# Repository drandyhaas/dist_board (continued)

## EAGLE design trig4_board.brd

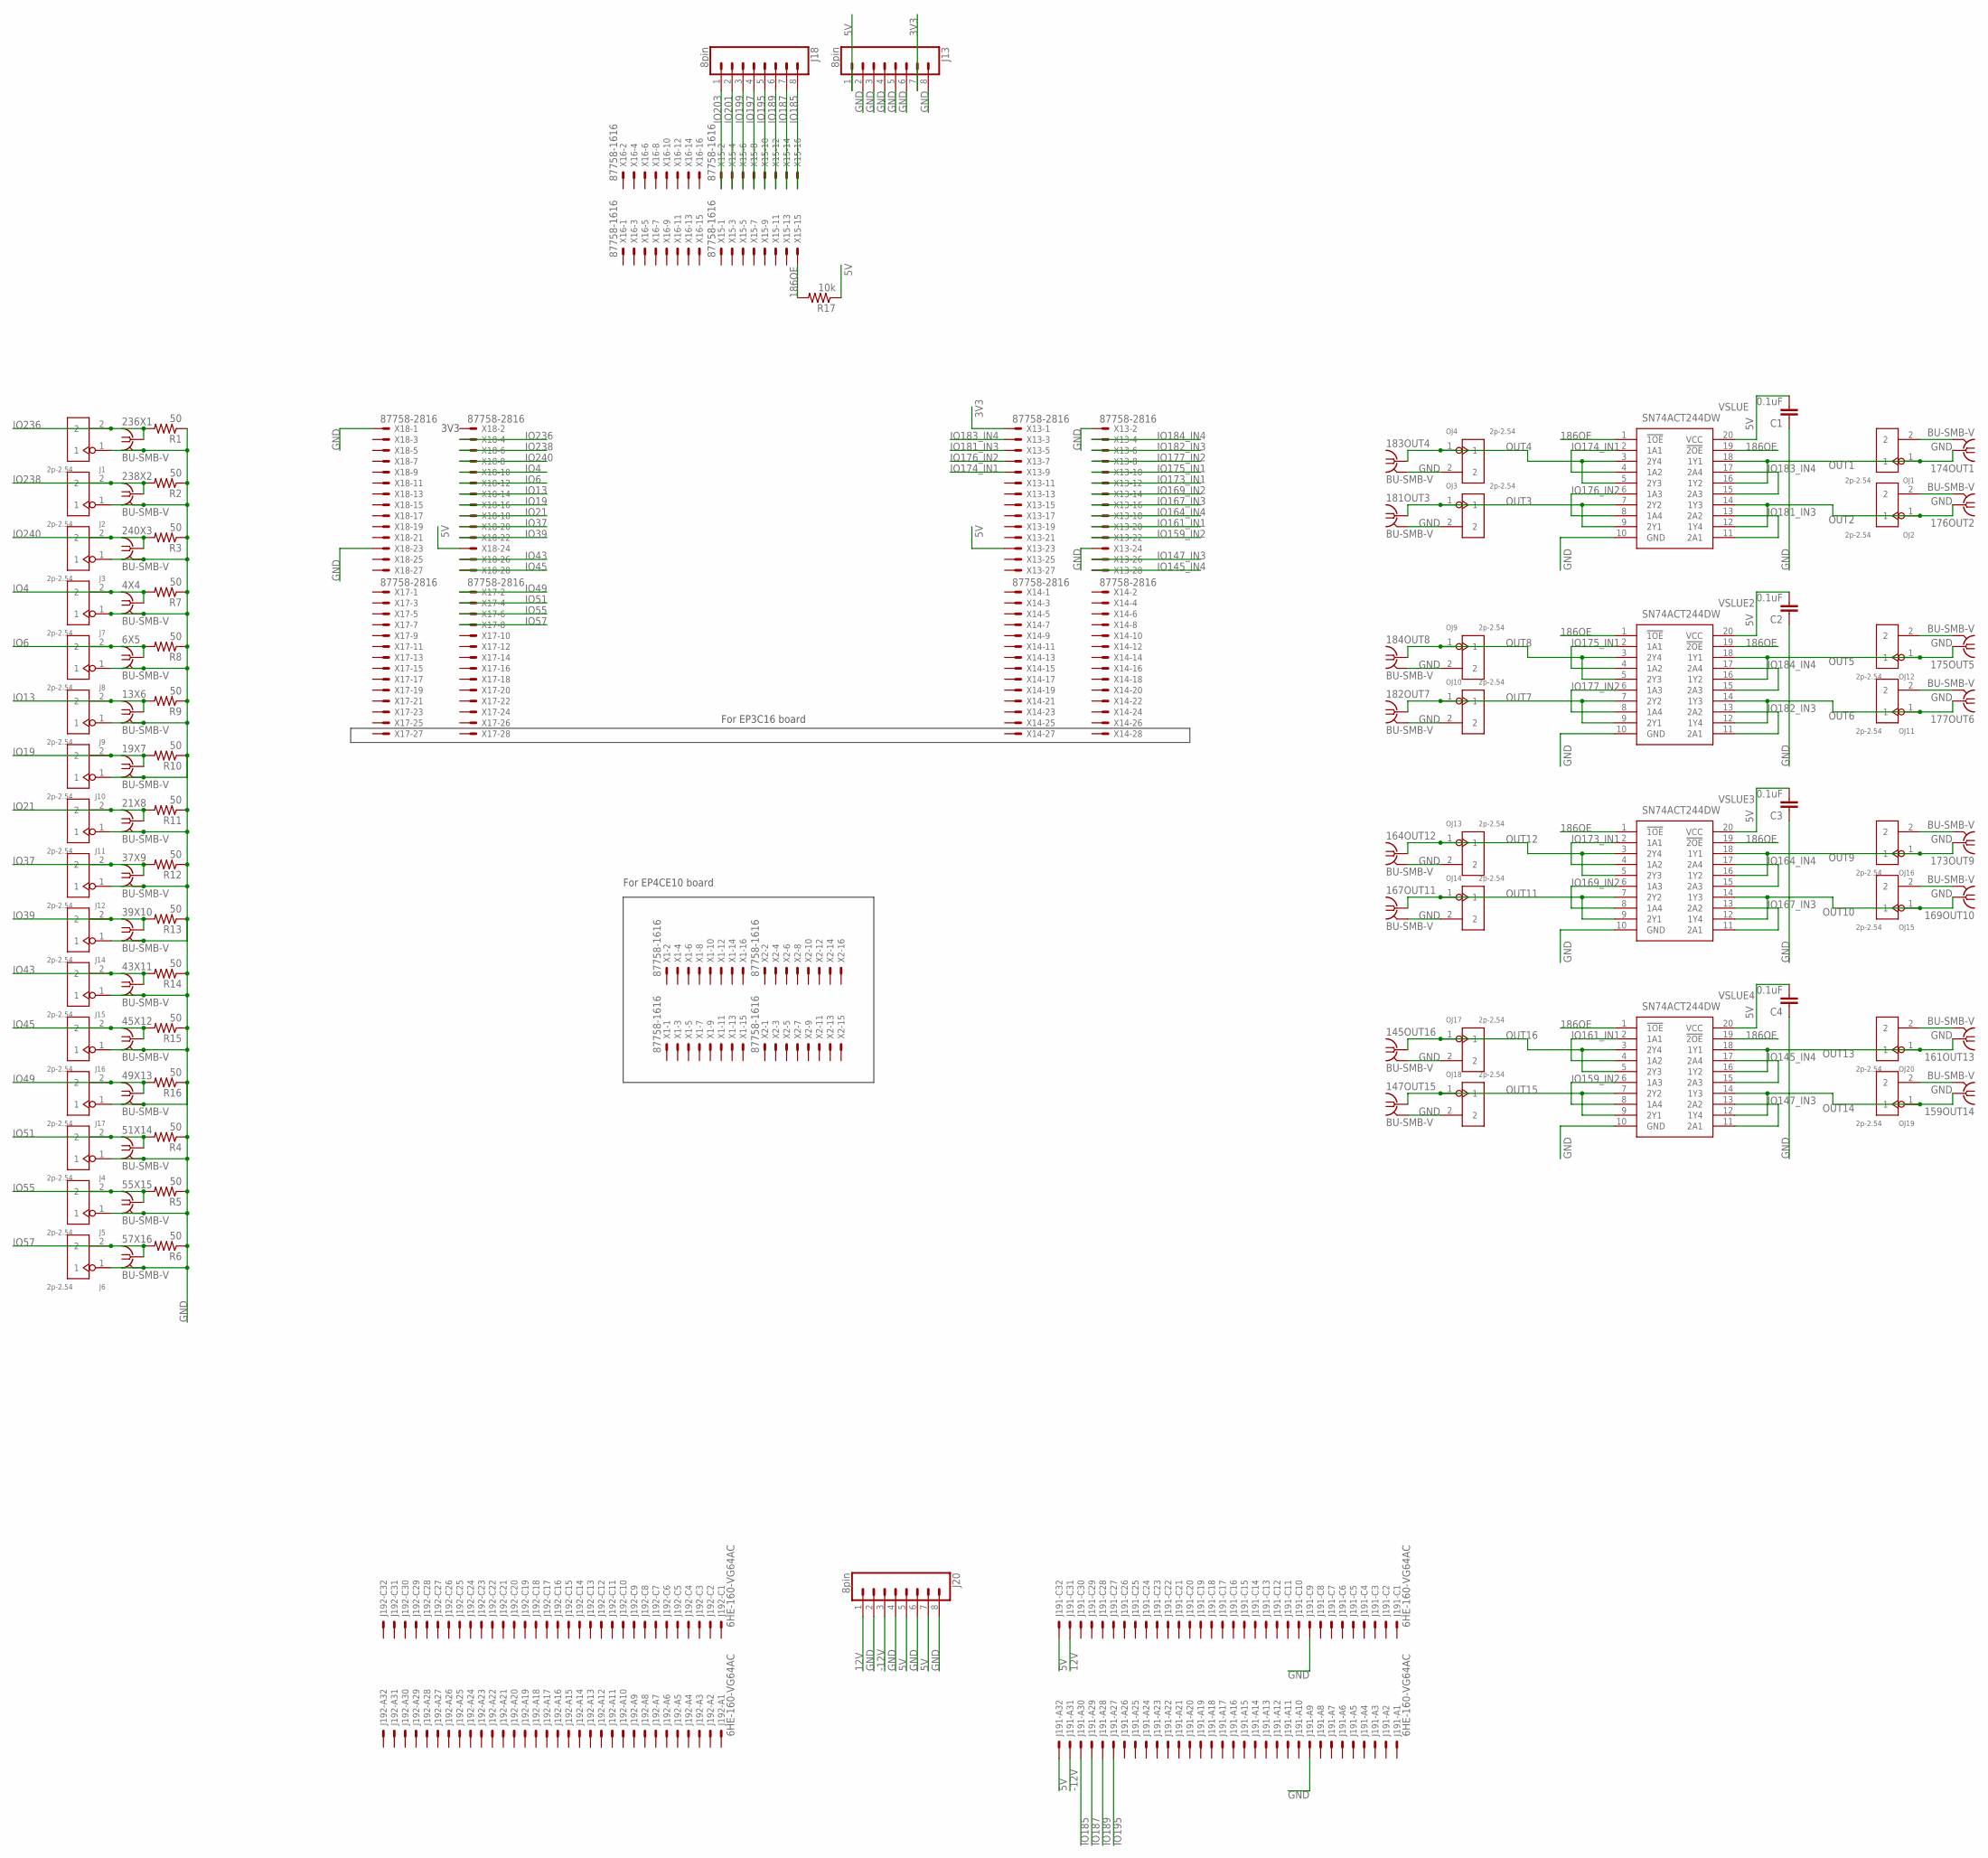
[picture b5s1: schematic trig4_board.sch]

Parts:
4X4, 6X5, 13X6, 19X7, 21X8, 37X9, 39X10, 43X11, 45X12, 49X13, 51X14, 55X15, 57X16, 145OUT16, 147OUT15, 159OUT14, 161OUT13, 164OUT12, 167OUT11, 169OUT10, 173OUT9, 174OUT1, 175OUT5, 176OUT2, 177OUT6, 181OUT3, 182OUT7, 183OUT4, 184OUT8, 236X1, 238X2, 240X3: BU-SMB-V
C1, C2, C3, C4: 0.1uF; 0805
J1, J2, J3, J4, J5, J6, J7, J8, J9, J10, J11, J12, J14, J15, J16, J17: 2p-2.54; H2-2.54
J13, J18, J20: 8pin; 1X08
J19: 6HE-160-VG64AC; 6HE_160-VG64AC
OJ1, OJ2, OJ3, OJ4, OJ9, OJ10, OJ11, OJ12, OJ13, OJ14, OJ15, OJ16, OJ17, OJ18, OJ19, OJ20: 2p-2.54; H2-2.54
R1, R2, R3, R4, R5, R6, R7, R8, R9, R10, R11, R12, R13, R14, R15, R16: 50; AXIAL-0.3
R17: 10k; AXIAL-0.3
VSLUE, VSLUE2, VSLUE3, VSLUE4: SN74ACT244DW; SOIC127P1030X265-20N
X1, X2, X15, X16: 87758-1616
X13, X14, X17, X18: 87758-2816

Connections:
3V3: J13.7, X13.1
5V: C1.2, C2.2, C3.2, C4.2, J13.1, J19.1-A32 (MS), J19.1-C32 (MS), J20.5, J20.7, R17.P$1 (1), VSLUE.20 (VCC), VSLUE2.20 (VCC), VSLUE3.20 (VCC), VSLUE4.20 (VCC), X13.23, X18.24
12V: J19.1-C31 (MS), J20.1
186OE: R17.P$2 (2), VSLUE.1 (!1OE), VSLUE.19 (!2OE), VSLUE2.1 (!1OE), VSLUE2.19 (!2OE), VSLUE3.1 (!1OE), VSLUE3.19 (!2OE), VSLUE4.1 (!1OE), VSLUE4.19 (!2OE), X15.15
-12V: J19.1-A31 (MS), J20.3
GND: 4X4.2, 4X4.3 (2), 4X4.4 (2), 4X4.5 (2), 6X5.2, 6X5.3 (2), 6X5.4 (2), 6X5.5 (2), 13X6.2, 13X6.3 (2), 13X6.4 (2), 13X6.5 (2), 19X7.2, 19X7.3 (2), 19X7.4 (2), 19X7.5 (2), 21X8.2, 21X8.3 (2), 21X8.4 (2), 21X8.5 (2), 37X9.2, 37X9.3 (2), 37X9.4 (2), 37X9.5 (2), 39X10.2, 39X10.3 (2), 39X10.4 (2), 39X10.5 (2), 43X11.2, 43X11.3 (2), 43X11.4 (2), 43X11.5 (2), 45X12.2, 45X12.3 (2), 45X12.4 (2), 45X12.5 (2), 49X13.2, 49X13.3 (2), 49X13.4 (2), 49X13.5 (2), 51X14.2, 51X14.3 (2), 51X14.4 (2), 51X14.5 (2), 55X15.2, 55X15.3 (2), 55X15.4 (2), 55X15.5 (2), 57X16.2, 57X16.3 (2), 57X16.4 (2), 57X16.5 (2), 145OUT16.2, 145OUT16.3 (2), 145OUT16.4 (2), 145OUT16.5 (2), 147OUT15.2, 147OUT15.3 (2), 147OUT15.4 (2), 147OUT15.5 (2), 159OUT14.2, 159OUT14.3 (2), 159OUT14.4 (2), 159OUT14.5 (2), 161OUT13.2, 161OUT13.3 (2), 161OUT13.4 (2), 161OUT13.5 (2), 164OUT12.2, 164OUT12.3 (2), 164OUT12.4 (2), 164OUT12.5 (2), 167OUT11.2, 167OUT11.3 (2), 167OUT11.4 (2), 167OUT11.5 (2), 169OUT10.2, 169OUT10.3 (2), 169OUT10.4 (2), 169OUT10.5 (2), 173OUT9.2, 173OUT9.3 (2), 173OUT9.4 (2), 173OUT9.5 (2), 174OUT1.2, 174OUT1.3 (2), 174OUT1.4 (2), 174OUT1.5 (2), 175OUT5.2, 175OUT5.3 (2), 175OUT5.4 (2), 175OUT5.5 (2), 176OUT2.2, 176OUT2.3 (2), 176OUT2.4 (2), 176OUT2.5 (2), 177OUT6.2, 177OUT6.3 (2), 177OUT6.4 (2), 177OUT6.5 (2), 181OUT3.2, 181OUT3.3 (2), 181OUT3.4 (2), 181OUT3.5 (2), 182OUT7.2, 182OUT7.3 (2), 182OUT7.4 (2), 182OUT7.5 (2), 183OUT4.2, 183OUT4.3 (2), 183OUT4.4 (2), 183OUT4.5 (2), 184OUT8.2, 184OUT8.3 (2), 184OUT8.4 (2), 184OUT8.5 (2), 236X1.2, 236X1.3 (2), 236X1.4 (2), 236X1.5 (2), 238X2.2, 238X2.3 (2), 238X2.4 (2), 238X2.5 (2), 240X3.2, 240X3.3 (2), 240X3.4 (2), 240X3.5 (2), C1.1, C2.1, C3.1, C4.1, J1.1, J2.1, J3.1, J4.1, J5.1, J6.1, J7.1, J8.1, J9.1, J10.1, J11.1, J12.1, J13.2, J13.3, J13.4, J13.5, J13.6, J13.8, J14.1, J15.1, J16.1, J17.1, J19.1-A9 (MS), J19.1-C9 (MS), J20.2, J20.4, J20.6, J20.8, OJ1.2, OJ2.2, OJ3.2, OJ4.2, OJ9.2, OJ10.2, OJ11.2, OJ12.2, OJ13.2, OJ14.2, OJ15.2, OJ16.2, OJ17.2, OJ18.2, OJ19.2, OJ20.2, R1.P$1 (1), R2.P$1 (1), R3.P$1 (1), R4.P$1 (1), R5.P$1 (1), R6.P$1 (1), R7.P$1 (1), R8.P$1 (1), R9.P$1 (1), R10.P$1 (1), R11.P$1 (1), R12.P$1 (1), R13.P$1 (1), R14.P$1 (1), R15.P$1 (1), R16.P$1 (1), VSLUE.10 (GND), VSLUE2.10 (GND), VSLUE3.10 (GND), VSLUE4.10 (GND), X13.2, X13.24, X18.1, X18.23
IO4: 4X4.1, J7.2, R7.P$2 (2), X18.10
IO6: 6X5.1, J8.2, R8.P$2 (2), X18.12
IO13: 13X6.1, J9.2, R9.P$2 (2), X18.14
IO19: 19X7.1, J10.2, R10.P$2 (2), X18.16
IO21: 21X8.1, J11.2, R11.P$2 (2), X18.18
IO37: 37X9.1, J12.2, R12.P$2 (2), X18.20
IO39: 39X10.1, J14.2, R13.P$2 (2), X18.22
IO43: 43X11.1, J15.2, R14.P$2 (2), X18.26
IO45: 45X12.1, J16.2, R15.P$2 (2), X18.28
IO49: 49X13.1, J17.2, R16.P$2 (2), X17.2
IO51: 51X14.1, J4.2, R4.P$2 (2), X17.4
IO55: 55X15.1, J5.2, R5.P$2 (2), X17.6
IO57: 57X16.1, J6.2, R6.P$2 (2), X17.8
IO145_IN4: VSLUE4.15 (2A3), VSLUE4.17 (2A4), X13.28
IO147_IN3: VSLUE4.11 (2A1), VSLUE4.13 (2A2), X13.26
IO159_IN2: VSLUE4.6 (1A3), VSLUE4.8 (1A4), X13.22
IO161_IN1: VSLUE4.2 (1A1), VSLUE4.4 (1A2), X13.20
IO164_IN4: VSLUE3.15 (2A3), VSLUE3.17 (2A4), X13.18
IO167_IN3: VSLUE3.11 (2A1), VSLUE3.13 (2A2), X13.16
IO169_IN2: VSLUE3.6 (1A3), VSLUE3.8 (1A4), X13.14
IO173_IN1: VSLUE3.2 (1A1), VSLUE3.4 (1A2), X13.12
IO174_IN1: VSLUE.2 (1A1), VSLUE.4 (1A2), X13.9
IO175_IN1: VSLUE2.2 (1A1), VSLUE2.4 (1A2), X13.10
IO176_IN2: VSLUE.6 (1A3), VSLUE.8 (1A4), X13.7
IO177_IN2: VSLUE2.6 (1A3), VSLUE2.8 (1A4), X13.8
IO181_IN3: VSLUE.11 (2A1), VSLUE.13 (2A2), X13.5
IO182_IN3: VSLUE2.11 (2A1), VSLUE2.13 (2A2), X13.6
IO183_IN4: VSLUE.15 (2A3), VSLUE.17 (2A4), X13.3
IO184_IN4: VSLUE2.15 (2A3), VSLUE2.17 (2A4), X13.4
IO185: J18.8, J19.1-A30 (MS), X15.16
IO187: J18.7, J19.1-A29 (MS), X15.14
IO189: J18.6, J19.1-A28 (MS), X15.12
IO195: J18.5, J19.1-A27 (MS), X15.10
IO197: J18.4, X15.8
IO199: J18.3, X15.6
IO201: J18.2, X15.4
IO203: J18.1, X15.2
IO236: 236X1.1, J1.2, R1.P$2 (2), X18.4
IO238: 238X2.1, J2.2, R2.P$2 (2), X18.6
IO240: 240X3.1, J3.2, R3.P$2 (2), X18.8
OUT1: 174OUT1.1, OJ1.1, VSLUE.16 (1Y2), VSLUE.18 (1Y1)
OUT2: 176OUT2.1, OJ2.1, VSLUE.12 (1Y4), VSLUE.14 (1Y3)
OUT3: 181OUT3.1, OJ3.1, VSLUE.7 (2Y2), VSLUE.9 (2Y1)
OUT4: 183OUT4.1, OJ4.1, VSLUE.3 (2Y4), VSLUE.5 (2Y3)
OUT5: 175OUT5.1, OJ12.1, VSLUE2.16 (1Y2), VSLUE2.18 (1Y1)
OUT6: 177OUT6.1, OJ11.1, VSLUE2.12 (1Y4), VSLUE2.14 (1Y3)
OUT7: 182OUT7.1, OJ10.1, VSLUE2.7 (2Y2), VSLUE2.9 (2Y1)
OUT8: 184OUT8.1, OJ9.1, VSLUE2.3 (2Y4), VSLUE2.5 (2Y3)
OUT9: 173OUT9.1, OJ16.1, VSLUE3.16 (1Y2), VSLUE3.18 (1Y1)
OUT10: 169OUT10.1, OJ15.1, VSLUE3.12 (1Y4), VSLUE3.14 (1Y3)
OUT11: 167OUT11.1, OJ14.1, VSLUE3.7 (2Y2), VSLUE3.9 (2Y1)
OUT12: 164OUT12.1, OJ13.1, VSLUE3.3 (2Y4), VSLUE3.5 (2Y3)
OUT13: 161OUT13.1, OJ20.1, VSLUE4.16 (1Y2), VSLUE4.18 (1Y1)
OUT14: 159OUT14.1, OJ19.1, VSLUE4.12 (1Y4), VSLUE4.14 (1Y3)
OUT15: 147OUT15.1, OJ18.1, VSLUE4.7 (2Y2), VSLUE4.9 (2Y1)
OUT16: 145OUT16.1, OJ17.1, VSLUE4.3 (2Y4), VSLUE4.5 (2Y3)

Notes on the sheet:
3V3
For EP4CE10 board
For EP3C16 board

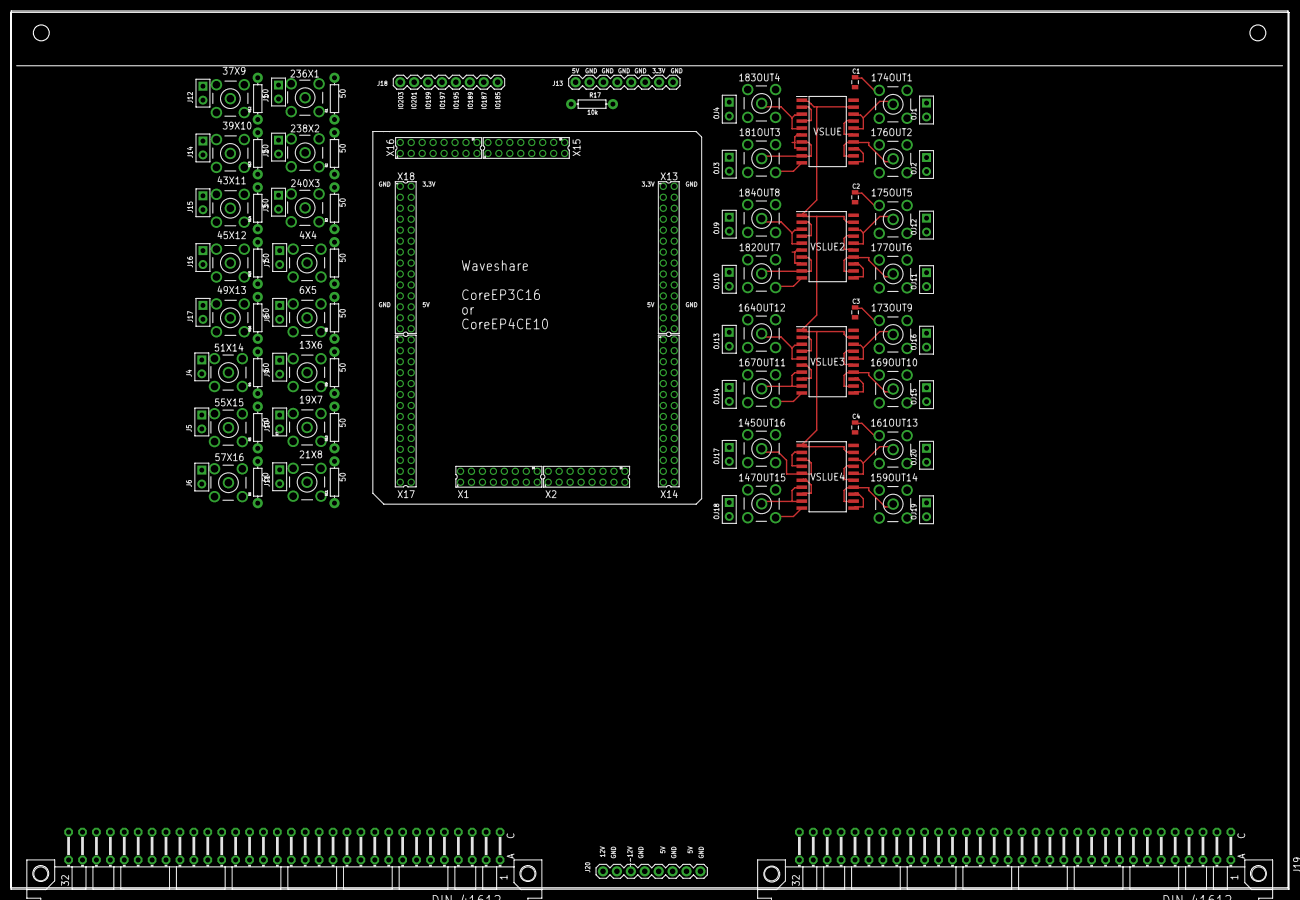
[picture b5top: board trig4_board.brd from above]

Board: 4 copper layers, 233.2 x 160.0 mm, 101 parts (0 on the bottom side), 62 nets.

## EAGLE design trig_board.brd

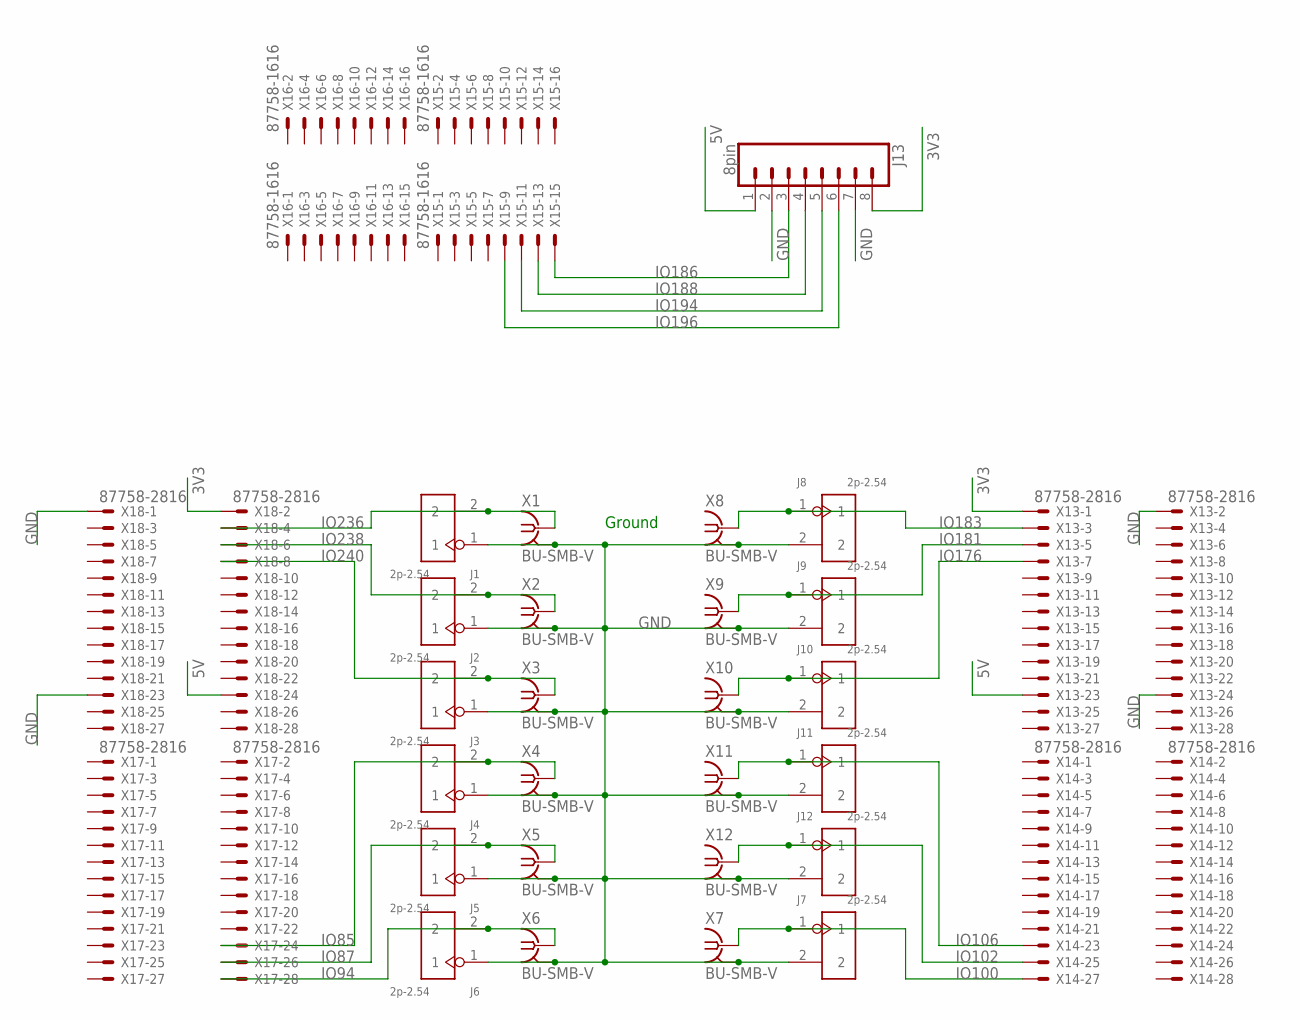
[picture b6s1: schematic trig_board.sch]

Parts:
J1, J2, J3, J4, J5, J6, J7, J8, J9, J10, J11, J12: 2p-2.54; H2-2.54
J13: 8pin; 1X08
X1, X2, X3, X4, X5, X6, X7, X8, X9, X10, X11, X12: BU-SMB-V
X13, X14, X17, X18: 87758-2816
X15, X16: 87758-1616

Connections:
3V3: J13.8, X13.1, X18.2
5V: J13.1, X13.23, X18.24
GND: J1.1, J2.1, J3.1, J4.1, J5.1, J6.1, J7.2, J8.2, J9.2, J10.2, J11.2, J12.2, J13.2, J13.7, X1.2, X1.3 (2), X1.4 (2), X1.5 (2), X2.2, X2.3 (2), X2.4 (2), X2.5 (2), X3.2, X3.3 (2), X3.4 (2), X3.5 (2), X4.2, X4.3 (2), X4.4 (2), X4.5 (2), X5.2, X5.3 (2), X5.4 (2), X5.5 (2), X6.2, X6.3 (2), X6.4 (2), X6.5 (2), X7.2, X7.3 (2), X7.4 (2), X7.5 (2), X8.2, X8.3 (2), X8.4 (2), X8.5 (2), X9.2, X9.3 (2), X9.4 (2), X9.5 (2), X10.2, X10.3 (2), X10.4 (2), X10.5 (2), X11.2, X11.3 (2), X11.4 (2), X11.5 (2), X12.2, X12.3 (2), X12.4 (2), X12.5 (2), X13.2, X13.24, X18.1, X18.23
IO85: J4.2, X4.1, X17.24
IO87: J5.2, X5.1, X17.26
IO94: J6.2, X6.1, X17.28
IO100: J7.1, X7.1, X14.27
IO102: J12.1, X12.1, X14.25
IO106: J11.1, X11.1, X14.23
IO176: J10.1, X10.1, X13.7
IO181: J9.1, X9.1, X13.5
IO183: J8.1, X8.1, X13.3
IO186: J13.3, X15.15
IO188: J13.4, X15.13
IO194: J13.5, X15.11
IO196: J13.6, X15.9
IO236: J1.2, X1.1, X18.4
IO238: J2.2, X2.1, X18.6
IO240: J3.2, X3.1, X18.8

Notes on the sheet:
Ground

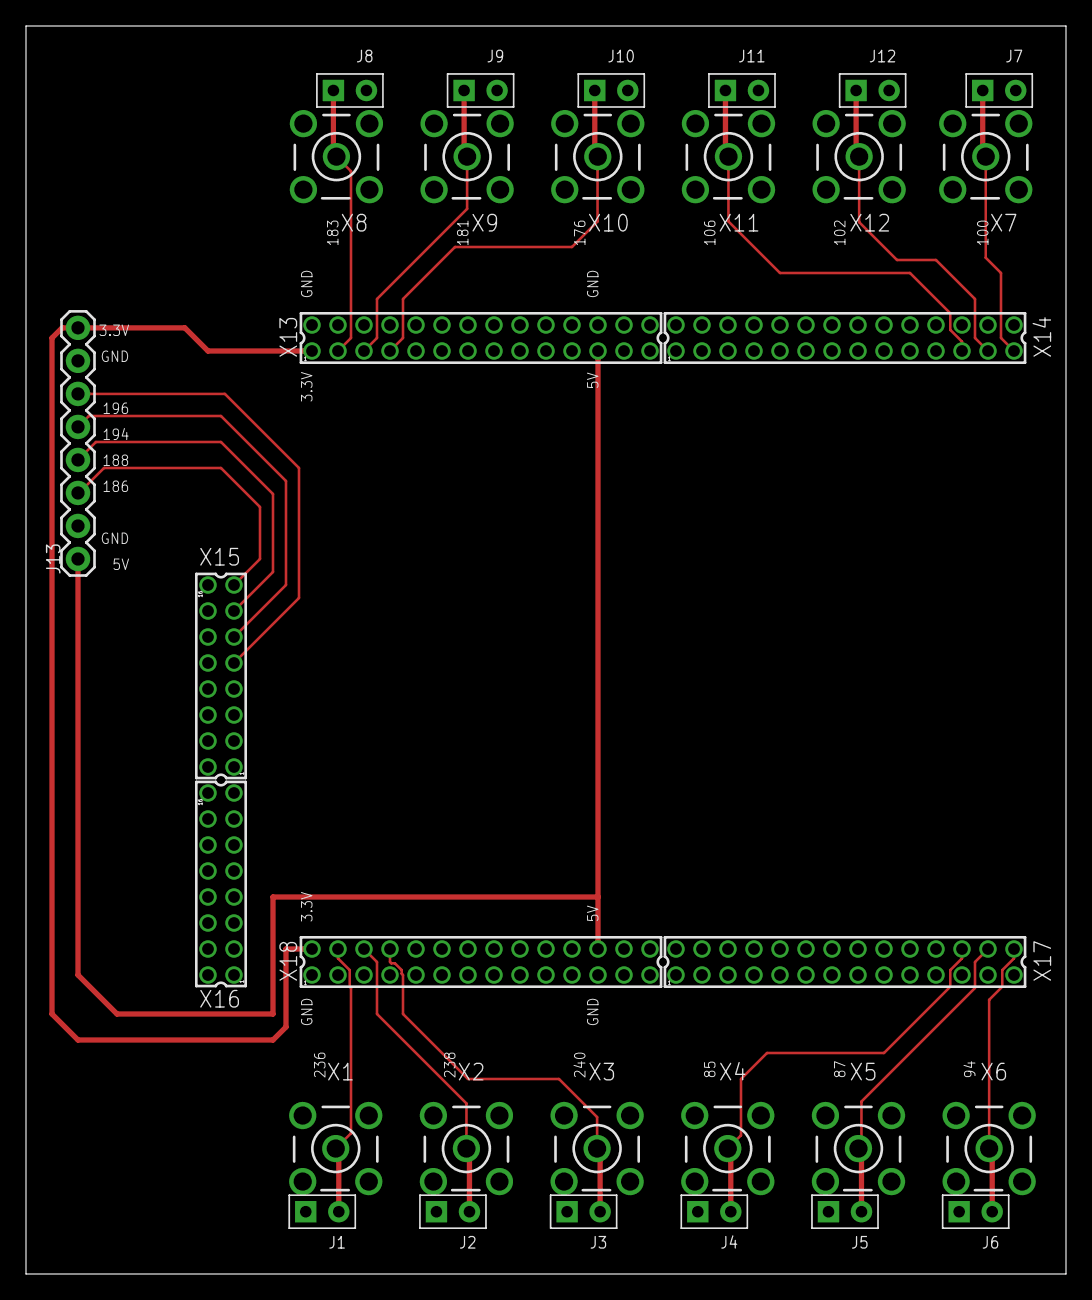
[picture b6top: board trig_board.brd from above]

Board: 2 copper layers, 80.0 x 96.0 mm, 31 parts (0 on the bottom side), 19 nets.

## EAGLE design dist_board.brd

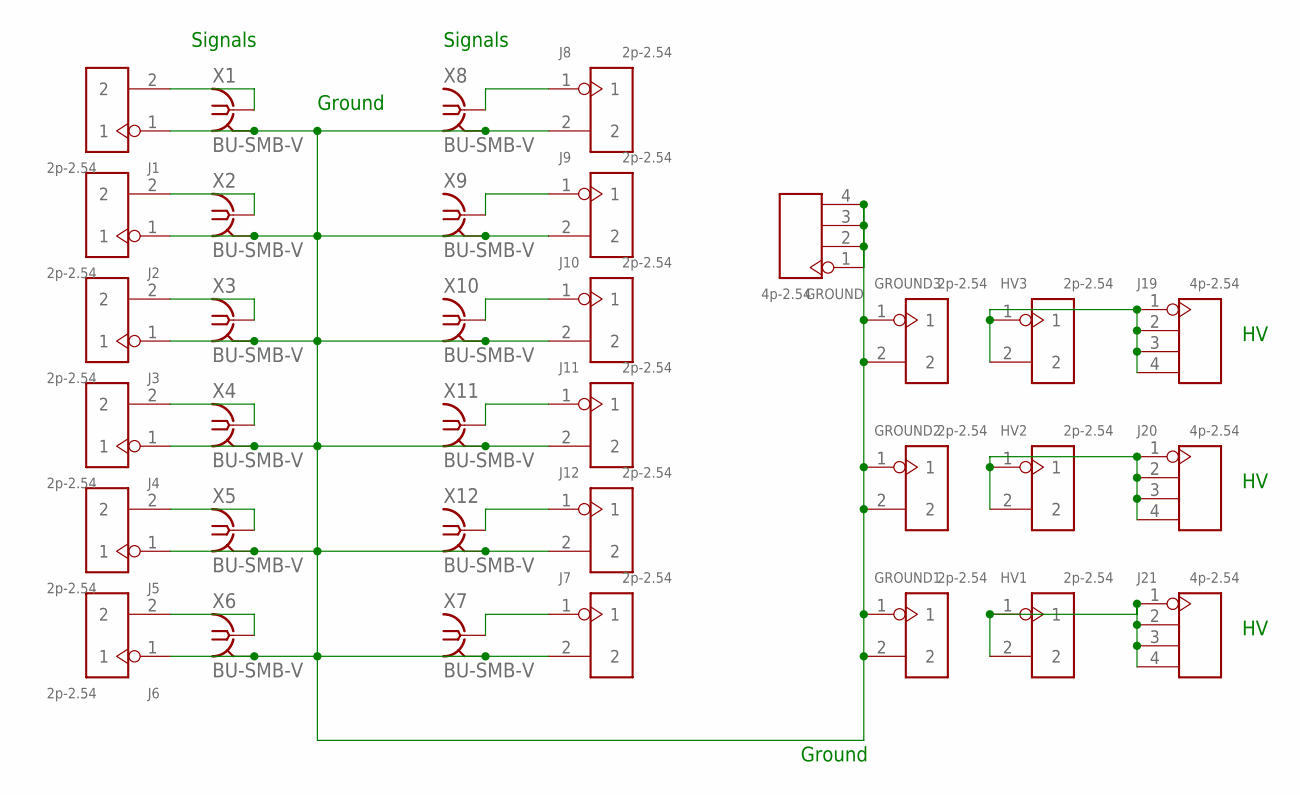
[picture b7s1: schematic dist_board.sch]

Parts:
GROUND: 4p-2.54; H4-2.54
GROUND1, GROUND2, GROUND3: 2p-2.54; H2-2.54
HV1, HV2, HV3: 2p-2.54; H2-2.54
J1, J2, J3, J4, J5, J6, J7, J8, J9, J10, J11, J12: 2p-2.54; H2-2.54
J19, J20, J21: 4p-2.54; H4-2.54
X1, X2, X3, X4, X5, X6, X7, X8, X9, X10, X11, X12: BU-SMB-V

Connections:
GND: GROUND.1, GROUND.2, GROUND.3, GROUND.4, GROUND1.1, GROUND1.2, GROUND2.1, GROUND2.2, GROUND3.1, GROUND3.2, J1.1, J2.1, J3.1, J4.1, J5.1, J6.1, J7.2, J8.2, J9.2, J10.2, J11.2, J12.2, X1.2, X1.3 (2), X1.4 (2), X1.5 (2), X2.2, X2.3 (2), X2.4 (2), X2.5 (2), X3.2, X3.3 (2), X3.4 (2), X3.5 (2), X4.2, X4.3 (2), X4.4 (2), X4.5 (2), X5.2, X5.3 (2), X5.4 (2), X5.5 (2), X6.2, X6.3 (2), X6.4 (2), X6.5 (2), X7.2, X7.3 (2), X7.4 (2), X7.5 (2), X8.2, X8.3 (2), X8.4 (2), X8.5 (2), X9.2, X9.3 (2), X9.4 (2), X9.5 (2), X10.2, X10.3 (2), X10.4 (2), X10.5 (2), X11.2, X11.3 (2), X11.4 (2), X11.5 (2), X12.2, X12.3 (2), X12.4 (2), X12.5 (2)
unnamed: J1.2, X1.1
unnamed: HV2.1, HV2.2, J20.1, J20.2, J20.3, J20.4
unnamed: J6.2, X6.1
unnamed: J5.2, X5.1
unnamed: J4.2, X4.1
unnamed: J3.2, X3.1
unnamed: J2.2, X2.1
unnamed: J8.1, X8.1
unnamed: J9.1, X9.1
unnamed: J10.1, X10.1
unnamed: J11.1, X11.1
unnamed: J12.1, X12.1
unnamed: J7.1, X7.1
unnamed: HV1.1, HV1.2, J21.1, J21.2, J21.3, J21.4
unnamed: HV3.1, HV3.2, J19.1, J19.2, J19.3, J19.4

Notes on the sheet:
Signals
Ground

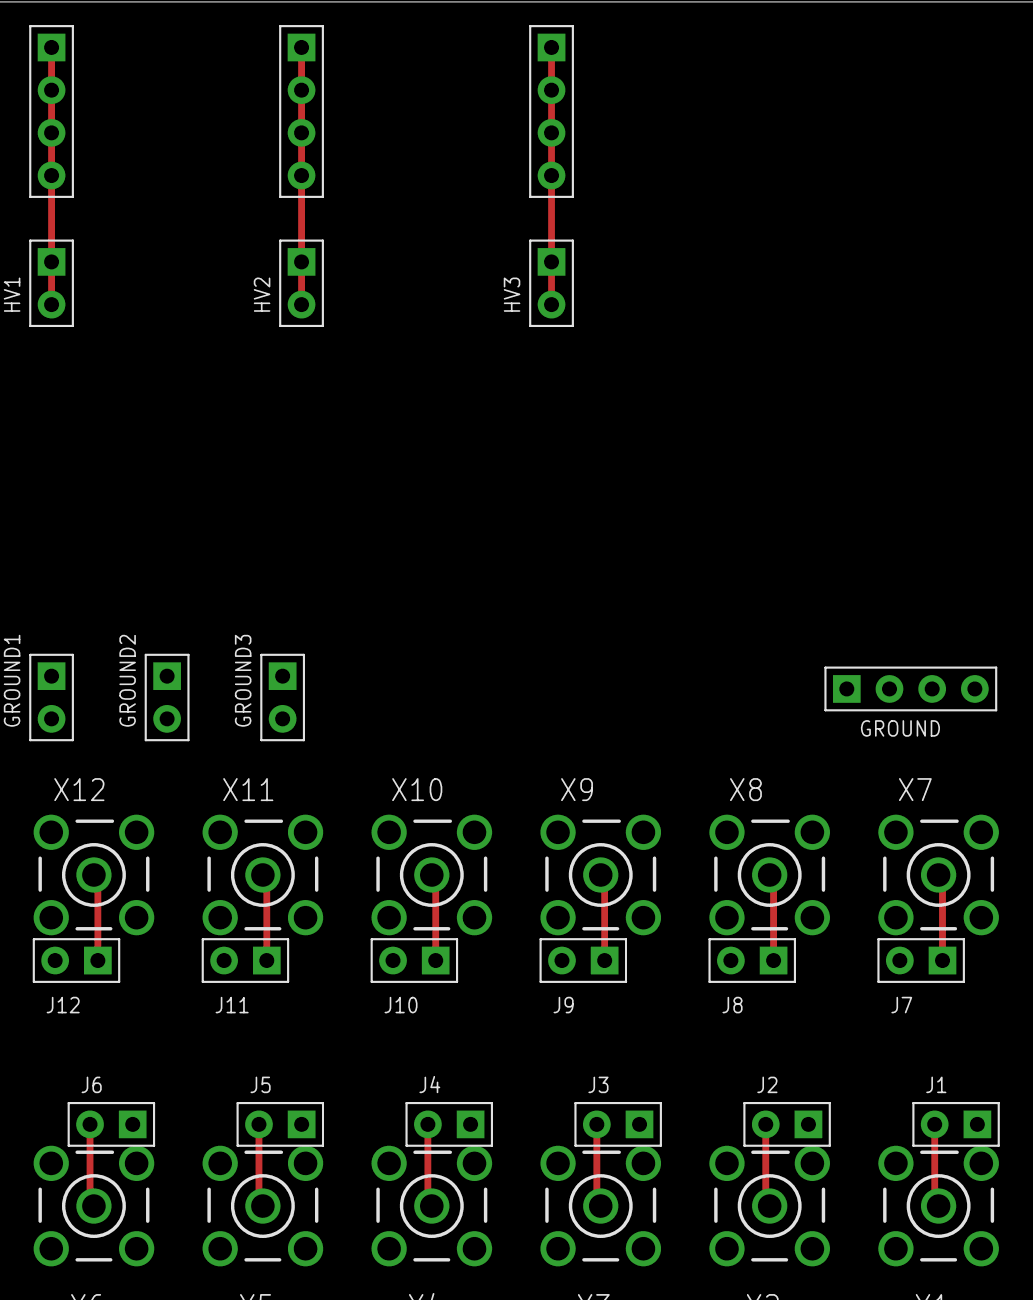
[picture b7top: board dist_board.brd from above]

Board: 2 copper layers, 34 parts (0 on the bottom side), 16 nets.

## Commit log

2018-05-31 initial
2018-05-31 measurements
2018-06-07 cleaned up component alignment, moved HV traces up
2018-06-07 rotated group back, added dimension measurement
2018-06-07 ready for ordering 1
2018-06-17 bigger hole for sma
2018-11-09 trigger board - ordered 10 on allpcb
2018-11-18 with ACT244 output drivers
2018-11-18 autorouted with topo
2018-11-27 with design block
2018-12-07 better routing
2019-01-10 16 inputs and 16 outputs
2019-01-18 firmware
2019-01-18 trig3 board, with pull up OE
2019-02-01 VME board, ordered from JLCPCB
2019-02-05 remove
2019-02-05 with +-12 V
2019-02-07 4 layer
2019-02-15 for win10 board
2019-02-18 new routing
2019-02-18 for 16 inputs and output enable
2019-02-19 add possibility of EP4CE10 board
2021-04-27 add work from 2019
2021-04-28 trigger board firmware
2021-04-28 ignore some firmware files for git
2021-04-28 project cleanup
2021-04-29 start with minimal functionality, equal to minimal branch
2021-04-29 minimal functionality
2021-04-29 minor
2021-04-29 serial talk working
2021-04-29 haasoscope add on with sma out
2021-04-30 trigout board
2021-05-01 working trigger decoding
2021-05-01 8 histos
2021-05-01 wait for normal triggers to stop before calibrating trigger bins
2021-05-02 report active clock
2021-05-02 low bandwidth clock for less jitter
2021-05-03 sync 16 trigger input channels
2021-05-04 send all delaycounters, can choose which histos from which channel to monitor
2021-05-05 be careful to sync in triggers using the same timing as the real triggers
2021-05-05 reset histos
2021-05-05 reset delaycounter to 0
2021-05-05 swap spare left and right, fix histos
2021-05-05 give ext_trig_out
2021-05-08 4 byte random seed
2021-05-08 prescale integer
2021-05-08 set prescale
2021-05-12 for prescale
2021-05-13 4 tick wide ext trig, rolling ext trig
2021-05-13 control rolling trigger
2021-05-21 rack version of de0 nano extender
2021-05-22 pass setup timing
2021-05-23 almost passes hold timing
2021-06-02 add 6mm on top and bottom, to fit in sliders
2021-06-14 961200 baud, and fix hold timing constraints by making in clocks logically exclusive groups
2021-07-02 Start of LVDS VME 6U board
2021-07-02 All major components
2021-07-02 Added 3v3 supplies
2021-07-02 routed
2021-07-02 add rects
2021-07-07 routed with gnd on layers 2 and 15
2021-07-07 removed old board and schematic files
2021-07-07 firmware for lvds board - use programming pins as regular IO after config
2021-07-07 try rj45 jack
2021-07-07 code for lvds board, using out10 as lvds test output (needs 3 ext resistors) go to 2.5 IO for everything, so we can use lvds output
2021-07-13 For test lvds board - takes 8 inputs closest to serial connection (IC1) and maps to coax_in(0-7), then fires coax_out(8)/N14 for 20*8ns if coax_in(0) has fired. Also uses coax_out(10) as a test lvds 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
2021-07-16 trig3 board waveshare
2021-07-16 better
2021-07-16 better, v1.43
2021-07-16 added 50 ohm term on extra sma inputs, v1.44
2021-07-17 initial waveshare trig3 board checkin
2021-07-26 working upload
2021-07-26 inputs 1-4 are trigger outputs and others are passthrough
2021-07-26 invert lvds inputs, so outputs are low by default
2021-09-15 simplify for documenting
2021-09-15 set prescale to 1, and adjust triedtofire
2021-09-15 lengthen output
2021-09-15 invert lvds inputs
2021-09-17 commands
2021-09-17 firmware v5 final, sending to OSU
2021-11-04 firmware v6 for sending to UCSB
2021-11-05 firmware v7, fix minor bug with first trigger that could be vetoed by debug trigger deadtime
2021-11-08 firmware v7, 64 LVDS inputs, and all io mapped
2021-11-08 firmware v7, 64 LVDS inputs, and all io mapped and used, passing timing
2021-11-10 firmware v7, add input trigger mask
2024-03-08 add some pics, and remove older stuff
